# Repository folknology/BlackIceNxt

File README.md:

# BlackIceNxt
BlackIce Nxt is a new systems board for the myStorm FPGA development board family. It sports the following features:
* STM32F730 216Mhz Arm Cortex 7 Microcontroller with 256K RAM, 64k Flash
* 64Mbit HypeRam, 128Mbit HyperFlash for the [MidPlane](https://github.com/folknology/IceLogicBus)
* 16Mbit SPI Flash for local storage
* 25Mhz HSE and 32.768Khz LSE crystals
* 40 Pin FMC Parallel interface expansion
* QSPI interface to [MidPlane](https://github.com/folknology/IceLogicBus)
* 4 Micro Blade sockets
* SDCard Socket
* SWD connector
* USB-C connector with serial over usb interface
* RGB Status LED and Mode button

### BlackIce Nxt PCB

### Top

### Bottom

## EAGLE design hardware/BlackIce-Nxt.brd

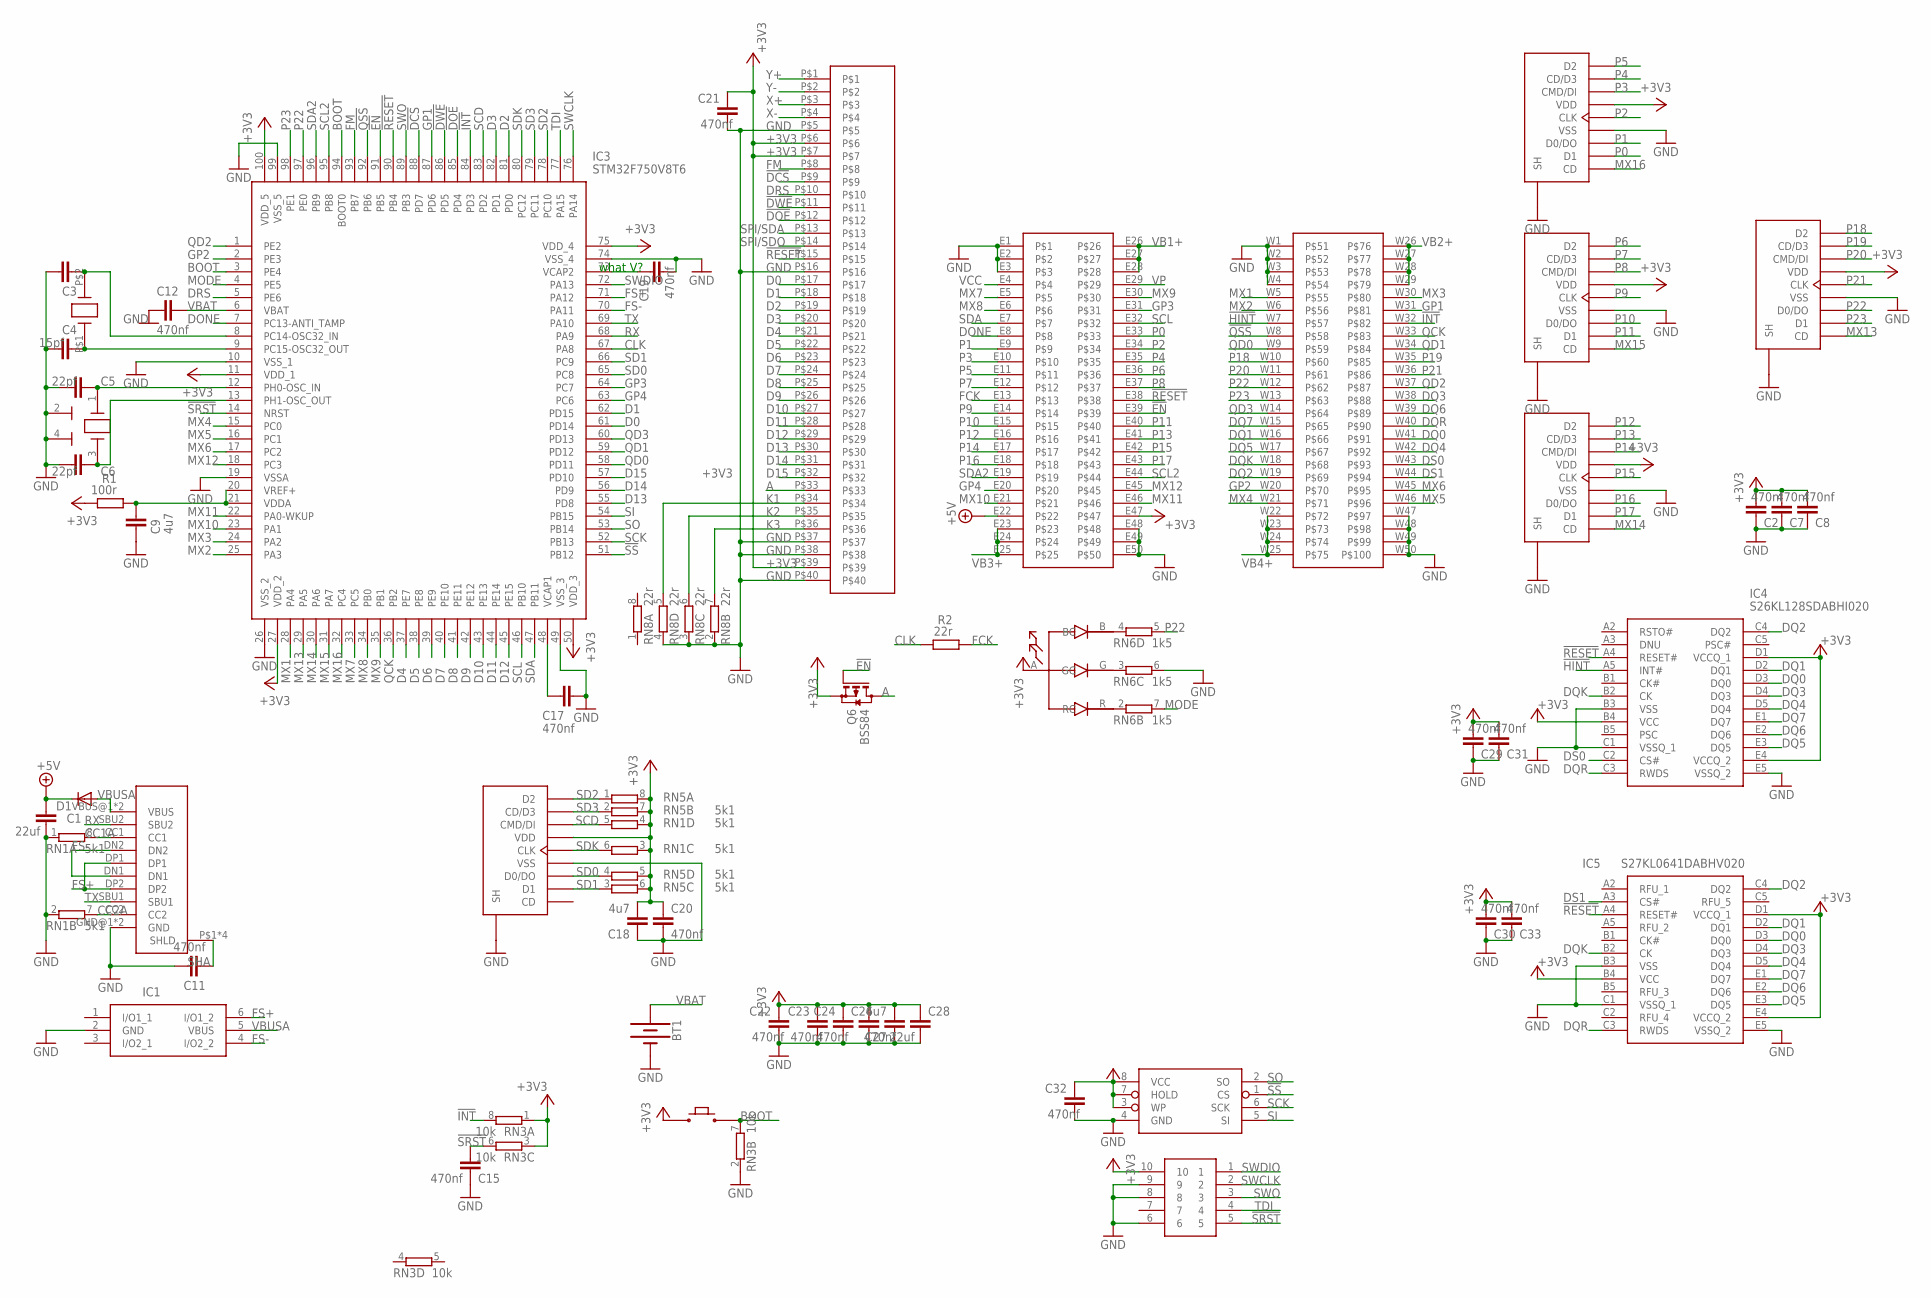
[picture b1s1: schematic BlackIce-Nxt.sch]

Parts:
B2: 4X3-RA-BUTTON
BT1: BATTERY-20MM_SMD; BATTCON_20MM
C1, C28: 22uf; C0603
C2, C7, C8, C11, C12, C15, C17, C19, C20, C21, C22, C23, C24, C26, C29, C30, C31, C32, C33: 470nf; C0402
C3, C4: 15pf; C0402
C5, C6: 22pf; C0402
C9, C18, C27: 4u7; C0402
C10: USB-C-16; USB-C
C16, C35, C36, C38, C41: TF-15X15; SDCARD
C25: XF2M-4015-1AFPC-0.5; XF2M-4015-1A
C34: 2X5-HEADER; 1.27-2X5-HEADER
D1: DIODE-SOD123; SOD123
IC1: USBLC6-2SC6; SOT95P280X145-6N
IC3: STM32F750V8T6; QFP50P1600X1600X160-100N
IC4: S26KL128SDABHI020; BGA24C100P5X5_600X800X100
IC5: S27KL0641DABHV020; BGA24C100P5X5_600X800X100
IC6: AT25SDF041A; SOIC-8-NARROW
L1: RGB_LED; RGB_LED_IMM
Q6: BSS84; SOT23
R1: 100r; R0402
R2: 22r; R0402
RN1, RN5: 5k1; EXB38V
RN3: 10k; EXB38V
RN6: 1k5; EXB38V
RN8: 22r; EXB38V
T1: MEZZANINEM-TILE; MEZZANINNE-T
X1: FC-135; FC135
X2: 12MZ; CRYSTAL-3.2X2.5

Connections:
!DCS: C25.P$9, IC3.88 (PD7)
!DOE: C25.P$12, IC3.85 (PD4)
!DWE: C25.P$11, IC3.86 (PD5)
!EN: IC3.91 (PB5), Q6.1 (G), T1.E39
!HINT: IC4.A5 (INT#), T1.W7
!INT: IC3.84 (PD3), RN3.8 (2), T1.W32
!QSS: IC3.92 (PB6), T1.W8
!RESET: C25.P$15, IC3.90 (PB4), IC4.A4 (RESET#), IC5.A4 (RESET#), T1.E38
!SRST: C15.2, C34.5, IC3.14 (NRST), RN3.6 (2)
!SS: IC3.51 (PB12), IC6.1 (CS)
+3V3: B2.P$1, C2.2, C7.2, C8.2, C16.P$6 (VDD), C18.2, C20.1, C21.1, C22.1, C23.1, C24.1, C25.P$6, C25.P$7, C25.P$39, C26.2, C27.2, C28.1, C29.2, C30.2, C31.2, C32.1, C33.2, C34.10, C35.P$6 (VDD), C36.P$6 (VDD), C38.P$6 (VDD), C41.P$6 (VDD), IC3.11 (VDD_1), IC3.27 (VDD_2), IC3.50 (VDD_3), IC3.75 (VDD_4), IC3.100 (VDD_5), IC4.B4 (VCC), IC4.D1 (VCCQ_1), IC4.E4 (VCCQ_2), IC5.B4 (VCC), IC5.D1 (VCCQ_1), IC5.E4 (VCCQ_2), IC6.3 (WP), IC6.7 (HOLD), IC6.8 (VCC), L1.A (ANODE), Q6.2 (S), R1.2, RN1.3 (1), RN1.4 (1), RN3.1, RN3.3 (1), RN5.5 (2), RN5.6 (2), RN5.7 (2), RN5.8 (2), T1.E47
+5V: C1.1, D1.C, T1.E22
A: C25.P$33, Q6.3 (D)
BOOT: B2.P$2, IC3.3 (PE4), IC3.94 (BOOT0), RN3.7 (2)
CC1A: C10.CC1, RN1.8 (2)
CC2A: C10.CC2, RN1.7 (2)
CLK: IC3.67 (PA8), R2.2
D0: C25.P$17, IC3.61 (PD14)
D1: C25.P$18, IC3.62 (PD15)
D2: C25.P$19, IC3.81 (PD0)
D3: C25.P$20, IC3.82 (PD1)
D4: C25.P$21, IC3.37 (PE7)
D5: C25.P$22, IC3.38 (PE8)
D6: C25.P$23, IC3.39 (PE9)
D7: C25.P$24, IC3.40 (PE10)
D8: C25.P$25, IC3.41 (PE11)
D9: C25.P$26, IC3.42 (PE12)
D10: C25.P$27, IC3.43 (PE13)
D11: C25.P$28, IC3.44 (PE14)
D12: C25.P$29, IC3.45 (PE15)
D13: C25.P$30, IC3.55 (PD8)
D14: C25.P$31, IC3.56 (PD9)
D15: C25.P$32, IC3.57 (PD10)
DONE: IC3.7 (PC13-ANTI_TAMP), T1.E8
DQ0: IC4.D3 (DQ0), IC5.D3 (DQ0), T1.W41
DQ1: IC4.D2 (DQ1), IC5.D2 (DQ1), T1.W16
DQ2: IC4.C4 (DQ2), IC5.C4 (DQ2), T1.W19
DQ3: IC4.D4 (DQ3), IC5.D4 (DQ3), T1.W38
DQ4: IC4.D5 (DQ4), IC5.D5 (DQ4), T1.W42
DQ5: IC4.E3 (DQ5), IC5.E3 (DQ5), T1.W17
DQ6: IC4.E2 (DQ6), IC5.E2 (DQ6), T1.W39
DQ7: IC4.E1 (DQ7), IC5.E1 (DQ7), T1.W15
DQK: IC4.B2 (CK), IC5.B2 (CK), T1.W18
DQR: IC4.C3 (RWDS), IC5.C3 (RWDS), T1.W40
DRS: C25.P$10, IC3.5 (PE6)
DS0: IC4.C2 (CS#), T1.W43
DS1: IC5.A3 (CS#), T1.W44
FCK: R2.1, T1.E13
FM: C25.P$8, IC3.93 (PB7)
FS+: C10.DP1, C10.DP2, IC1.6 (I/O1_2), IC3.71 (PA12)
FS-: C10.DN1, C10.DN2, IC1.4 (I/O2_2), IC3.70 (PA11)
GND: BT1.2 (-), C1.2, C2.1, C3.1, C4.1, C5.1, C6.1, C7.1, C8.1, C9.2, C10.GND@1 (GND), C10.GND@2 (GND), C11.1, C12.2, C15.1, C16.P$4 (VSS), C16.P$10 (SH), C16.P$11 (SH), C16.P$12 (SH), C16.P$13 (SH), C17.1, C18.1, C19.2, C20.2, C21.2, C22.2, C23.2, C24.2, C25.P$5, C25.P$16, C25.P$37, C25.P$38, C25.P$40, C26.1, C27.1, C28.2, C29.1, C30.1, C31.1, C32.2, C33.1, C34.6, C34.8, C34.9, C35.P$4 (VSS), C35.P$10 (SH), C35.P$11 (SH), C35.P$12 (SH), C35.P$13 (SH), C36.P$4 (VSS), C36.P$10 (SH), C36.P$11 (SH), C36.P$12 (SH), C36.P$13 (SH), C38.P$4 (VSS), C38.P$10 (SH), C38.P$11 (SH), C38.P$12 (SH), C38.P$13 (SH), C41.P$4 (VSS), C41.P$10 (SH), C41.P$11 (SH), C41.P$12 (SH), C41.P$13 (SH), IC1.2 (GND), IC3.10 (VSS_1), IC3.19 (VSSA), IC3.26 (VSS_2), IC3.49 (VSS_3), IC3.74 (VSS_4), IC3.99 (VSS_5), IC4.B3 (VSS), IC4.C1 (VSSQ_1), IC4.E5 (VSSQ_2), IC5.B3 (VSS), IC5.C1 (VSSQ_1), IC5.E5 (VSSQ_2), IC6.4 (GND), RN1.1, RN1.2 (1), RN3.2 (1), RN6.6 (2), RN8.2 (1), RN8.3 (1), RN8.4 (1), T1.E1, T1.E2, T1.E3, T1.E48, T1.E49, T1.E50, T1.W1, T1.W2, T1.W3, T1.W4, T1.W47, T1.W48, T1.W49, T1.W50, X2.2 (GND), X2.4 (GND)
GP1: IC3.87 (PD6), T1.W31
GP2: IC3.2 (PE3), T1.W20
GP3: IC3.64 (PC7), T1.E31
GP4: IC3.63 (PC6), T1.E20
K1: C25.P$34, RN8.5 (2)
K2: C25.P$35, RN8.6 (2)
K3: C25.P$36, RN8.7 (2)
MODE: IC3.4 (PE5), RN6.7 (2)
MX1: IC3.28 (PA4), T1.W5
MX2: IC3.25 (PA3), T1.W6
MX3: IC3.24 (PA2), T1.W30
MX4: IC3.15 (PC0), T1.W21
MX5: IC3.16 (PC1), T1.W46
MX6: IC3.17 (PC2), T1.W45
MX7: IC3.33 (PC5), T1.E5
MX8: IC3.34 (PB0), T1.E6
MX9: IC3.35 (PB1), T1.E30
MX10: IC3.23 (PA1), T1.E21
MX11: IC3.22 (PA0-WKUP), T1.E46
MX12: IC3.18 (PC3), T1.E45
MX13: C41.P$1 (CD), IC3.29 (PA5)
MX14: C36.P$1 (CD), IC3.30 (PA6)
MX15: C38.P$1 (CD), IC3.31 (PA7)
MX16: C35.P$1 (CD), IC3.32 (PC4)
unnamed: L1.G (GC), RN6.3 (1)
unnamed: L1.R (RC), RN6.2 (1)
unnamed: L1.B (BC), RN6.4 (1)
unnamed: C6.2, IC3.13 (PH1-OSC_OUT), X2.3 (X2)
unnamed: C5.2, IC3.12 (PH0-OSC_IN), X2.1 (X1)
unnamed: C4.2, IC3.9 (PC15-OSC32_OUT), X1.P$1 (X1)
unnamed: C3.2, IC3.8 (PC14-OSC32_IN), X1.P$2 (X2)
unnamed: C19.1, IC3.73 (VCAP2)
unnamed: C17.2, IC3.48 (VCAP1)
unnamed: C9.1, IC3.20 (VREF+), IC3.21 (VDDA), R1.1
P0: C35.P$2 (D1), T1.E33
P1: C35.P$3 (D0/DO), T1.E9
P2: C35.P$5 (CLK), T1.E34
P3: C35.P$7 (CMD/DI), T1.E10
P4: C35.P$8 (CD/D3), T1.E35
P5: C35.P$9 (D2), T1.E11
P6: C38.P$9 (D2), T1.E36
P7: C38.P$8 (CD/D3), T1.E12
P8: C38.P$7 (CMD/DI), T1.E37
P9: C38.P$5 (CLK), T1.E14
P10: C38.P$3 (D0/DO), T1.E15
P11: C38.P$2 (D1), T1.E40
P12: C36.P$9 (D2), T1.E16
P13: C36.P$8 (CD/D3), T1.E41
P14: C36.P$7 (CMD/DI), T1.E17
P15: C36.P$5 (CLK), T1.E42
P16: C36.P$3 (D0/DO), T1.E18
P17: C36.P$2 (D1), T1.E43
P18: C41.P$9 (D2), T1.W10
P19: C41.P$8 (CD/D3), T1.W35
P20: C41.P$7 (CMD/DI), T1.W11
P21: C41.P$5 (CLK), T1.W36
P22: C41.P$3 (D0/DO), IC3.97 (PE0), RN6.5 (2), T1.W12
P23: C41.P$2 (D1), IC3.98 (PE1), T1.W13
QCK: IC3.36 (PB2), T1.W33
QD0: IC3.58 (PD11), T1.W9
QD1: IC3.59 (PD12), T1.W34
QD2: IC3.1 (PE2), T1.W37
QD3: IC3.60 (PD13), T1.W14
RX: C10.SBU2, IC3.68 (PA9)
SCD: C16.P$7 (CMD/DI), IC3.83 (PD2), RN1.5 (2)
SCK: IC3.52 (PB13), IC6.6 (SCK)
SCL: IC3.46 (PB10), T1.E32
SCL2: IC3.95 (PB8), T1.E44
SD0: C16.P$3 (D0/DO), IC3.65 (PC8), RN5.4 (1)
SD1: C16.P$2 (D1), IC3.66 (PC9), RN5.3 (1)
SD2: C16.P$9 (D2), IC3.78 (PC10), RN5.1
SD3: C16.P$8 (CD/D3), IC3.79 (PC11), RN5.2 (1)
SDA: IC3.47 (PB11), T1.E7
SDA2: IC3.96 (PB9), T1.E19
SDK: C16.P$5 (CLK), IC3.80 (PC12), RN1.6 (2)
SHA: C10.P$1 (SHLD), C10.P$2 (SHLD), C10.P$3 (SHLD), C10.P$4 (SHLD), C11.2
SI: IC3.54 (PB15), IC6.5 (SI)
SO: IC3.53 (PB14), IC6.2 (SO)
SPI/SDA: C25.P$13
SPI/SDO: C25.P$14
SWCLK: C34.2, IC3.76 (PA14)
SWDIO: C34.1, IC3.72 (PA13)
SWO: C34.3, IC3.89 (PB3)
TDI: C34.4, IC3.77 (PA15)
TX: C10.SBU1, IC3.69 (PA10)
VB1+: T1.E26, T1.E27, T1.E28
VB2+: T1.W26, T1.W27, T1.W28, T1.W29
VB3+: T1.E23, T1.E24, T1.E25
VB4+: T1.W22, T1.W23, T1.W24, T1.W25
VBAT: BT1.1 (+), C12.1, IC3.6 (VBAT)
VBUSA: C10.VBUS@1 (VBUS), C10.VBUS@2 (VBUS), D1.A, IC1.5 (VBUS)
VCC: T1.E4
VP: T1.E29
X+: C25.P$3
X-: C25.P$4
Y+: C25.P$1
Y-: C25.P$2

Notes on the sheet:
what V?

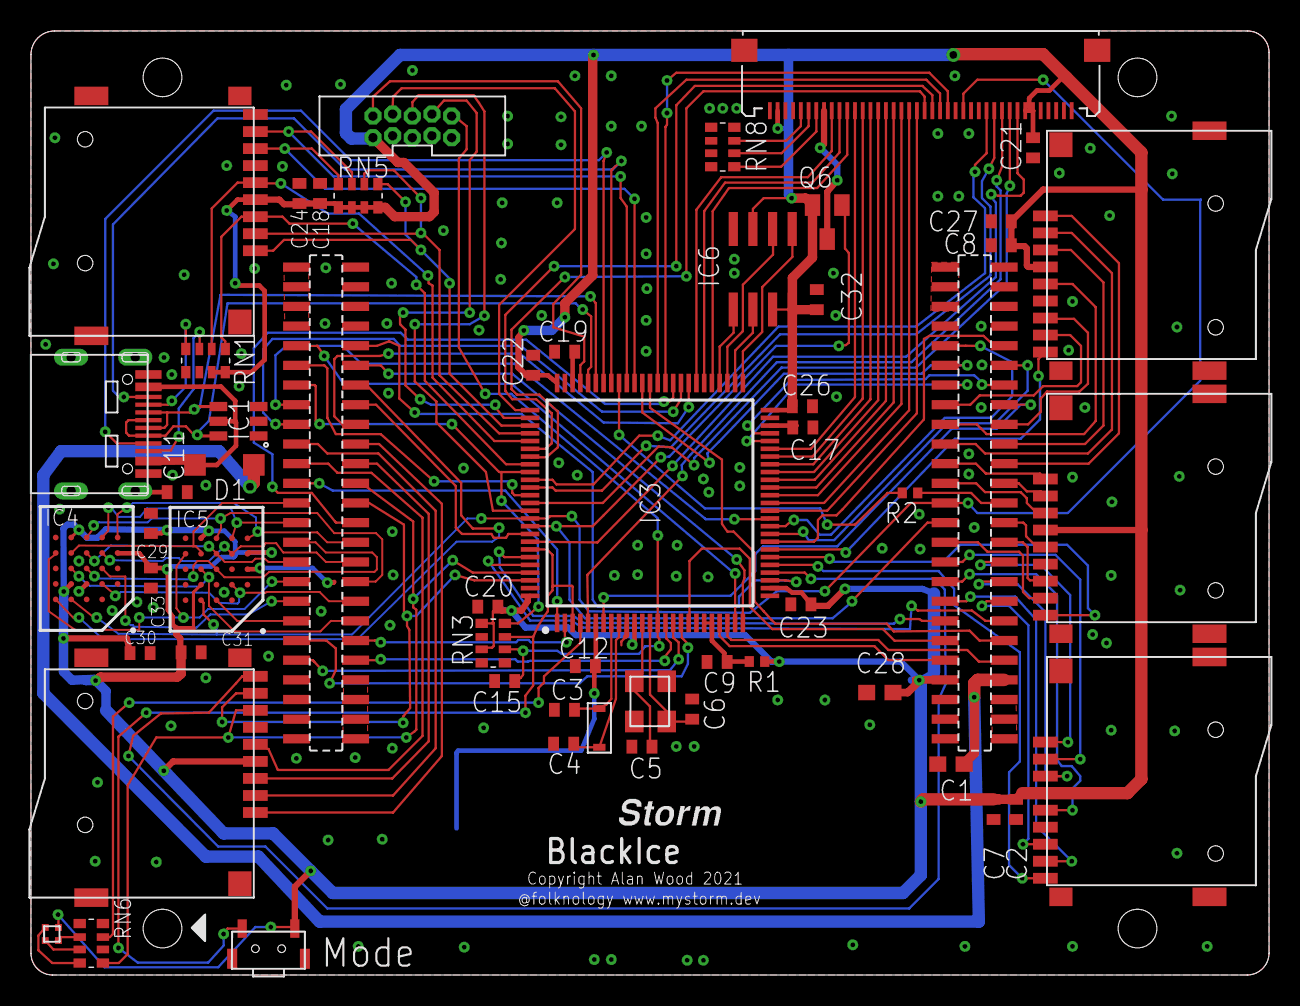
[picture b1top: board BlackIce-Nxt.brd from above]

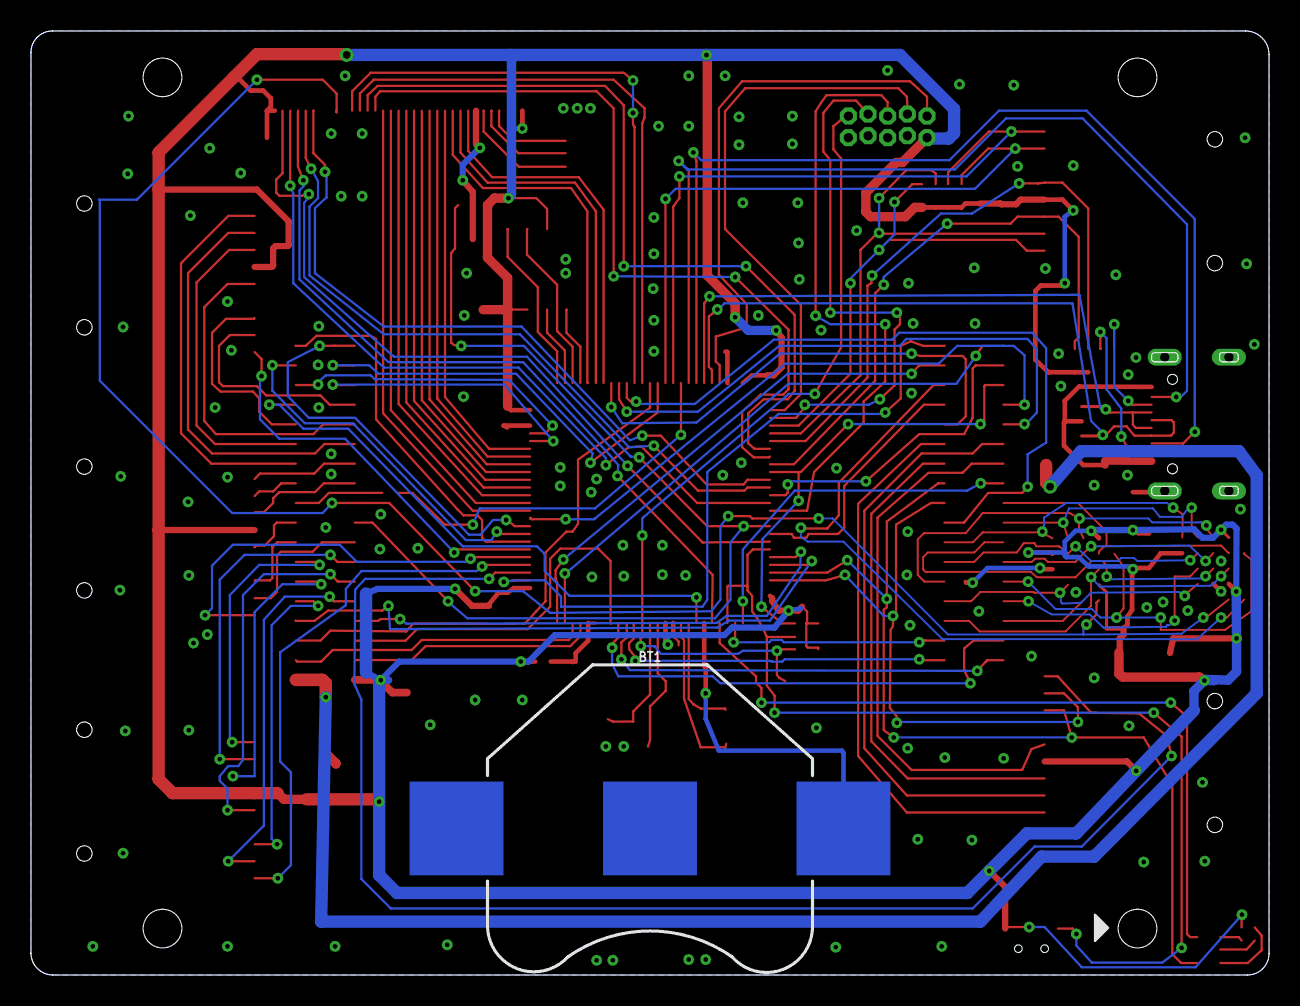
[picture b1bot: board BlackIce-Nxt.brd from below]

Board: 2 copper layers, 80.0 x 61.0 mm, 56 parts (3 on the bottom side), 141 nets.

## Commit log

2022-05-15 Added CAD files, images and descriptions
2022-05-15 Updated description to point to IceLogicBus MidPlane
2022-05-15 Corrected description typos
2022-05-15 Corrected more description typos
2022-07-21 Added history
2022-07-21 Added history Pics
2022-07-21 Edited markdown to correct titles
2022-07-21 Added URL

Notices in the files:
hardware/BlackIce-Nxt.brd:
Copyright Alan Wood 2021
parts and their libraries:
SparkFun-Batteries: Licensing: Creative Commons ShareAlike 4.0 International - https://creativecommons.org/licenses/by-sa/4.0
